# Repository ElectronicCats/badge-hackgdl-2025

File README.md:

# Badge HackGDL 2025

<p align="center">
    
</p>

<p align=center>
    
</p>

Welcome to the official repository of the Hack GDL 2025 event badge, developed by Electronic Cats. This portable device is designed to be interactive, educational, and hackable. It is based on the [Minino](https://github.com/ElectronicCats/Minino) platform, which uses ESP-IDF as the development environment and offers a modular system for creating BLE and Wi-Fi applications.

## Features:
- ESP32-S3
- Bluetooth Low Energy (BLE) + Wi-Fi
- USB-C for power and programming
- 4 x physical buttons for interaction
- 3 neopixel
- Integrated OLED Screen
- 3x AAA Battery Holder
- 1 x Buzzer
- Shitty Addon Connector
- Case
- Based on [Minino](https://github.com/ElectronicCats/Minino), with a modular architecture for multiple apps

## Included Applications:
These applications are ready-to-use and serve as a base for creating your own ideas during the event.
- Bluetooth (BLE) Applications
- Wi-Fi Applications
- Digital Tamagotchi

## Flashing Firmware:
Your badge should come with the latest firmware. If an update is required, this section of the wiki will explain how to flash your badge with the latest firmware. 

### Bootloader mode

To be able to flash your board, you will need to understand how to put it into bootloader mode. You just need to follow the sequence below:

* Press and hold the **BOOT** button
* Press and release the **RST** button
* Release the **BOOT** button

### ESP Tool (Web) update

1. Download the latest firmware from the [releases](https://github.com/ElectronicCats/badge-hackgdl-2025/releases) section.

2. Extract the downloaded file.

3. Open your web browser and go to [ESP Tool](https://espressif.github.io/esptool-js/).

4. Connect your badge to your computer using a USB cable and enter [bootloader mode](https://github.com/ElectronicCats/badge-hackgdl-2025/edit/main/README.md#bootloader-mode). 

5. Once on the page, in the baud rate, select 460800 and click on the “Connect” button.

6. You will see a pop-up window asking you to select the port where your badge is detected. Choose the one labeled “USB JTAG/serial debug unit.”

7. Once your badge is connected, the website will display the “Flash Address” field. Enter 0x0 in that field.

8. Click on “Select File” and look for the files in the unzipped folder. You must match the file and address according to the following table:

| Flash Address | File                 |
|---------------|----------------------|
| 0x0           | HackGDL_2025.bin |

9. Once you have all the files, click on “Program.” Wait until the process ends, or you read the message “Leaving...” in the output console.

10. When the program is finished, click on the “Disconnect” button.
11. Reset your HackGDL 2025 badge.

### Using the console

>[!IMPORTANT]
> [esptool.py](https://pypi.org/project/esptool/) is required.

To update your badge’s firmware, follow these steps:

1. Download the latest firmware from the [releases](https://github.com/ElectronicCats/badge-hackgdl-2025/releases).

3. Extract the downloaded file.

3. Open a terminal and navigate to the extracted folder. Make sure you see the HackGDL_2025.bin file.

4. Connect your badge to your computer using a USB cable and enter [bootloader mode](https://github.com/ElectronicCats/badge-hackgdl-2025/edit/main/README.md#bootloader-mode). Then check the port it is connected to.
    - **Windows**: Check it in the Device Manager under the Ports section.
    - **Linux**: check it with the `ls /dev/ttyUSB*` or `ls /dev/ttyACM*` command.
    - **macOS**: Check it with the `ls /dev/cu.usb*` command.

5. Run the following command to flash the firmware:

```python
python -m esptool --chip esp32s3 -b 460800 --before default_reset --after hard_reset write_flash --flash_mode dio --flash_size 4MB --flash_freq 80m 0x0 HackGDL_2025.bin
```

## Development Reference:

To compile, modify, or develop new applications for this badge, follow the official [Minino firmware development guide](https://github.com/ElectronicCats/Minino/tree/main/firmware).

> [!NOTE]  
> Although the Minino platform was designed for ESP32-C6, the HackGDL 2025 badge uses an ESP32-S3 as the main microcontroller. Make sure to configure the correct chip target in your development environment.

It includes:
ESP-IDF installation (v5.1.2)
Environment setup
Firmware compilation
Modular app structure
Flash and monitor commands

## FAQs
**Does the badge work out of the box?**

Yes. It comes with functional BLE and WiFi-based apps pre-installed.

**Can I develop my own app?**

Absolutely! Use Minino’s modular system and examples as a starting point.

**Where can I get help?**

Check the Minino wiki or open an issue [here](https://github.com/ElectronicCats/badge-hackgdl-2025/issues).

## Gratitude
Do you want to say thank you? Tag these companies on social networks and show them your badge, thanks to them, it is possible

- [ElectronicCats](https://electroniccats.com/)
- [HackGDL](https://hackgdl.net/)
- [Project TamaLib: A hardware-agnostic first-gen Tamagotchi emulation library](https://github.com/jcrona/tamalib)

## License

Electronic Cats invests time and resources providing this open source design, please support Electronic Cats and open-source hardware by purchasing products from Electronic Cats!

Designed by Electronic Cats.

Firmware released under an GNU AGPL v3.0 license. See the LICENSE file for more information.

Hardware released under an CERN Open Hardware License v1.2. See the LICENSE_HARDWARE file for more information.

Electronic Cats is a registered trademark, please do not use if you sell these PCBs.

Nov 29 2022

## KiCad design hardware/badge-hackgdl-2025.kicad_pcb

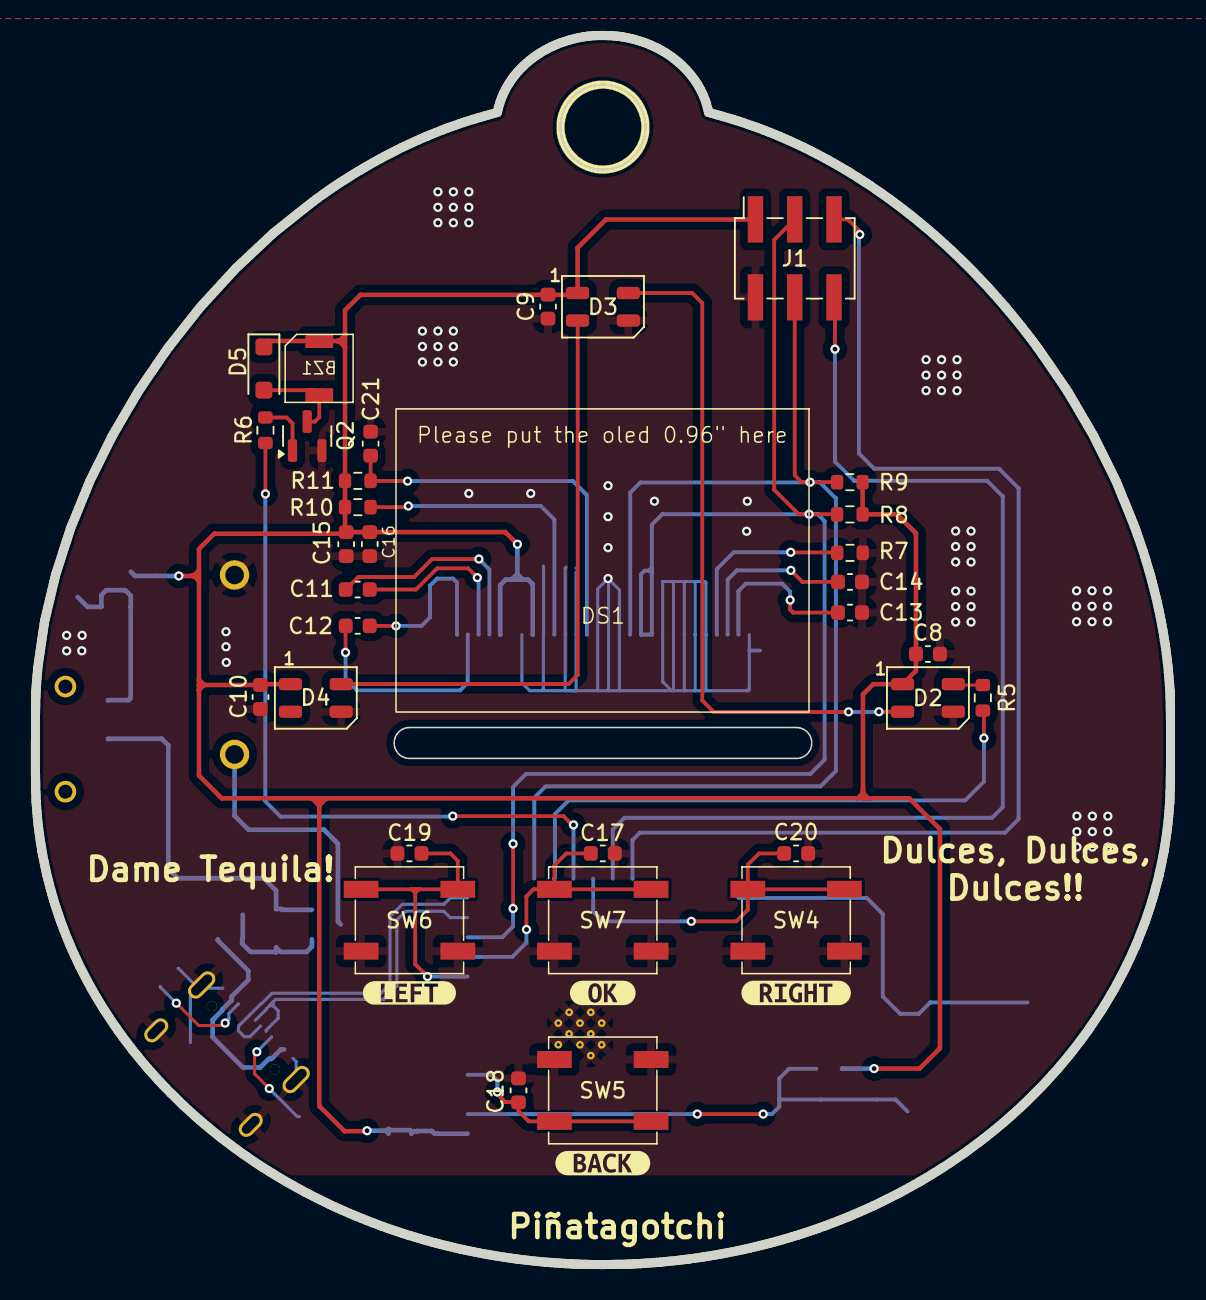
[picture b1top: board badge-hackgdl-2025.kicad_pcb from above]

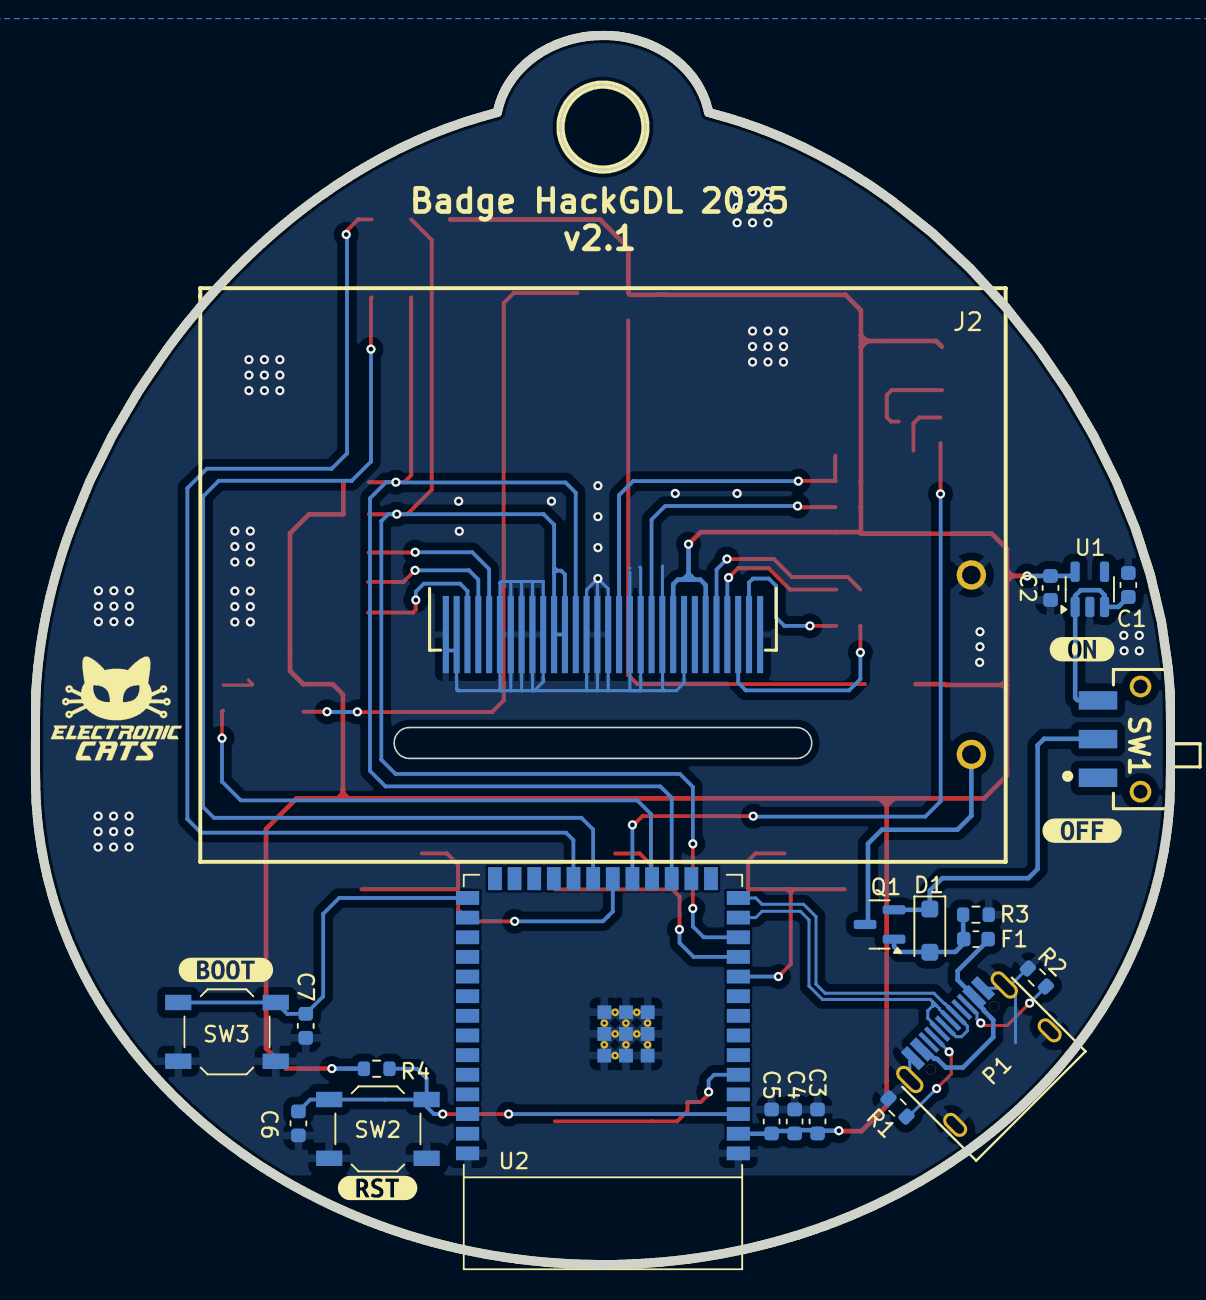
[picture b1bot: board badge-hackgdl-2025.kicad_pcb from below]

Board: 11 copper layers, 73.4 x 79.5 mm, 64 parts (26 on the bottom side), 37 nets.

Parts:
BZ1: Buzzer; Buzzer4x4
C1, C2, C4, C5, C13, C14, C16: 10uF; C_0603_1608Metric
C3, C11, C12: 1uF; C_0603_1608Metric
C6, C7, C8, C9, C10, C15, C17, C18, C19, C20: 100nF; C_0603_1608Metric
C21: 4.7uF; C_0603_1608Metric
D1, D5: MBR120; D_SOD-123F
D2, D3, D4: WS2812B; LED_WS2812B-Mini_PLCC4_3.5x3.5mm
DS1: OLED-128O064D; ssd1306_oled_conn_through_the_oled
F1: 1A; Fuse_0603_1608Metric
J1: ADDON; PinSocket_2x03_P2.54mm_Vertical_SMD
J2: Battery; BAT-TH_BH-AAA-A1AJ024
P1: USB_C_Plug_USB2.0; C393939
Q1: DMG3415U-7; SOT-23
Q2: MMBT2222A; SOT-23
R1, R2: 5k1; R_0603_1608Metric
R3: 100K; R_0603_1608Metric
R4, R8, R9, R10, R11: 10k; R_0603_1608Metric
R5: 470; R_0603_1608Metric
R6: 1K; R_0603_1608Metric
R7: 390k; R_0603_1608Metric
Ref**: Val**; badge-hackgdl-2025-Edge_Cuts
Ref**#2: Val**; badge-hackgdl-2025-Edge_Cuts
SW1: ON; JS102011SAQN
SW2: RESET; SW_SPST_TL3342
SW3: BOOT; SW_SPST_TL3342
SW4: RIGHT; Button_6.6x6.5
SW5: BACK; Button_6.6x6.5
SW6: LEFT; Button_6.6x6.5
SW7: MIDDLE; Button_6.6x6.5
U1: XC6220B331MR-G; SOT-23-5
U2: ESP32-S3-WROOM-1-N4; ESP32-S3-WROOM-1
kibuzzard-67883A3F: G***; kibuzzard-67883A3F
kibuzzard-67883A4C: G***; kibuzzard-67883A4C
kibuzzard-678830B0: G***; kibuzzard-678830B0
kibuzzard-678830B8: G***; kibuzzard-678830B8
kibuzzard-678830ED: G***; kibuzzard-678830ED
kibuzzard-678830F7: G***; kibuzzard-678830F7
kibuzzard-6789895F: G***; kibuzzard-6789895F
kibuzzard-67898922: G***; kibuzzard-67898922

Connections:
+3V3: BZ1.1 (-), C2.1, C3.1, C4.1, C5.1, C8.2, C9.2, C10.2, C15.1, C16.1, D2.1 (VDD), D3.1 (VDD), D4.1 (VDD), D5.1 (K), DS1.6 (VBAT), DS1.9 (VDD), J1.1, R4.2, R8.2, R9.2, R10.2, R11.2, U1.5 (VOUT), U2.2 (3V3)
+BATT: J2.2, Q1.3 (D)
/BACK: C18.1, SW5.2, U2.5 (IO5)
/BOOT: C7.1, SW3.2, U2.27 (IO0)
/Buzz: R6.1, U2.19 (IO11)
/D+: P1.A6 (D+), U2.14 (IO20)
/D-: P1.A7 (D-), U2.13 (IO19)
/GPIO1: J1.5, U2.22 (IO14)
/GPIO2: J1.6, U2.21 (IO13)
/LEFT: C19.1, SW6.2, U2.10 (IO17)
/MIDDLE: C17.1, SW7.2, U2.11 (IO18)
/NEOPIXEL: R5.1, U2.18 (IO10)
/RIGHT: C20.1, SW4.2, U2.20 (IO12)
/RST: C6.1, R4.1, SW2.2, U2.3 (EN)
/SCL: DS1.18 (D0), J1.4, R9.1, U2.17 (IO9)
/SDA: DS1.19 (D1), DS1.20 (D2), J1.3, R8.1, U2.12 (IO8)
GND: C1.2, C2.2, C3.2, C4.2, C5.2, C6.2, C7.2, C8.1, C9.1, C10.1, C13.1, C14.2, C15.2, C16.2, C17.2, C18.2, C19.2, C20.2, C21.2, D2.3 (VSS), D3.3 (VSS), D4.3 (VSS), DS1.1 (GND), DS1.8 (VSS), DS1.10 (BS0), DS1.12 (BS2), DS1.13 (~CS), DS1.15 (D/~C), DS1.16 (R/~W), DS1.17 (E/~RD), DS1.21 (D3), DS1.22 (D4), DS1.23 (D5), DS1.24 (D6), DS1.25 (D7), DS1.29 (VLSS), DS1.30 (GND), J1.2, J2.1, P1.A1 (GND), P1.S1 (SHIELD), Q2.2 (E), R1.1, R2.1, R3.2, R7.2, SW2.1, SW3.1, SW4.1, SW5.1, SW6.1, SW7.1, U1.2 (GND), U2.1 (GND), U2.40 (GND), U2.41 (GND)
unnamed: BZ1.2 (+), D5.2 (A), Q2.3 (C)
unnamed: D1.1 (K), Q1.2 (S), SW1.2 (B)
unnamed: D2.4 (DIN), R5.2
unnamed: D2.2 (DOUT), D3.4 (DIN)
unnamed: D3.2 (DOUT), D4.4 (DIN)
unnamed: DS1.11 (BS1), R10.1
unnamed: C11.1, DS1.5 (C1N)
unnamed: C11.2, DS1.4 (C1P)
unnamed: C12.2, DS1.2 (C2N)
unnamed: C12.1, DS1.3 (C2P)
unnamed: DS1.26 (IREF), R7.1
unnamed: C13.2, DS1.28 (VCC)
unnamed: C14.1, DS1.27 (VCOMH)
unnamed: C21.1, DS1.14 (~RES), R11.1
unnamed: F1.1, P1.A4 (VBUS)
unnamed: P1.A5 (CC), R1.2
unnamed: P1.B5 (VCONN), R2.2
unnamed: Q2.1 (B), R6.2
unnamed: C1.1, SW1.3 (A), U1.1 (VIN), U1.3 (EN)
VBUS: D1.2 (A), F1.2, Q1.1 (G), R3.1

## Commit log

2024-12-27 feat: add kicad project files
2024-12-27 feat: github actions modified
2024-12-27 feat(hw): add componnets for usb and microcontroller
2024-12-27 feat: Update gitignore
2024-12-27 refactor: delete backups
2024-12-27 feat(hw): add neopixels in the schematic
2024-12-27 feat(hw): add buttons and buzzer
2024-12-27 feat: add oled connector
2024-12-30 feat: add components in schematic
2025-01-03 feat: firmware setup
2025-01-03 feat: add components
2025-01-03 feat: add tamalib port for IDF
2025-01-03 feat: update dependencies & cmakelists
2025-01-03 feat: update tamalib_idf component cmakelists
2025-01-03 feat(hw): add floor plan
2025-01-03 feat: add tamagotchi app
2025-01-03 feat: add input queue
2025-01-06 feat: add menus navigation
2025-01-06 feat: add main icos
2025-01-06 feat(hw): add 3d models
2025-01-06 feat: add GPIOs shittyaddon connector
2025-01-07 refactor: simplify display code
2025-01-07 refactor: port tamagotchi display to mininos screen driver
2025-01-07 refactor: port menu navigation screen
2025-01-07 refactor: tamagotchi selection screen port
2025-01-08 feat(hw): update bom
2025-01-08 feat(hw): add 3d model for switch
2025-01-08 refactor: improve tamagotchi screen refresh to avoid alliasing
2025-01-08 feat: add generals & tamagotchi settings
2025-01-08 feat(hw): change oled footprint
2025-01-08 feat(hw): move buttons
2025-01-08 feat: improve menus UI
2025-01-08 refactor: general knob & general submenu to horizontal
2025-01-09 refactor: general radio selection UI to horizontal
2025-01-09 refactor: remove radio selection test code
2025-01-09 feat: add wifi apps
2025-01-09 feat: add BLE apps
2025-01-09 feat: launch BLE apps from menu
2025-01-09 refactor: menus & submenus UI
2025-01-10 feat: scrolling text to horizontal
2025-01-10 feat: add animations
2025-01-10 fix: tamagotchi display selection bitmaps
2025-01-10 refactor: summary scrolling text
2025-01-10 feat(hw): add routes in pcb
2025-01-13 refactor: notification function name
2025-01-13 refactor: HID app using generals
2025-01-13 feat: add general notification
2025-01-13 feat(hw): change ON/OFF switch
2025-01-13 refactor: HID menus
2025-01-13 fix: general notification bugs
2025-01-13 refactor: adv scanner using generals
2025-01-14 fix: general knob exit
2025-01-14 feat(hw): add labels
2025-01-14 feat(hw): change size of pads in the oled footprint
2025-01-14 feat(hw): change routes in oled
2025-01-14 refactor: trakers module
2025-01-14 refactor: deauth main menu
2025-01-14 refactor: deauth ap selection
2025-01-14 refactor: deauth attack selection
2025-01-14 feat: improve deauth main menu feeling
2025-01-14 refactor: deauth captive portal selection UI
2025-01-14 refactor: captive portal input
2025-01-14 refactor(hw): move buttons
2025-01-15 feat(hw): add space between buttons
2025-01-15 fix(hw): change gpio pins for addon connector
2025-01-15 fix(hw): change left button to gpio 17
2025-01-15 feat: improve main app scenes feeling
2025-01-15 fix: trakers count
2025-01-15 feat(hw): add capacitor in reset pin
2025-01-15 feat: trakers list bug test
2025-01-15 fix: deauth Rogue AP attack
2025-01-15 feat(hw): change LDO position
2025-01-15 feat(hw): change F1 position
2025-01-15 feat(hw): case parts
2025-01-15 feat: add wifi apps icons
2025-01-16 feat(hw): increase tolerances
2025-01-16 feat: add bluetooth apps icons
2025-01-16 feat: add rectangle on menu icons
2025-01-16 feat (hw): increase lid height
2025-01-16 feat: add neopixels
2025-01-16 refactor: change neopixels count
2025-01-16 refactor: tamagotchi UI
2025-01-17 feat: add set tama nickname cmd
2025-01-17 feat: save nickname in flash memory
2025-01-21 feat: add espnow connection
2025-01-21 feat: using espnow without dependencies
2025-01-22 feat: add tamagotchi friends logic
2025-01-22 feat: tamagotchi friends found logic
2025-01-22 feat: display friends count
2025-01-22 fix: avoid empty macs
2025-01-22 feat: show friends list
2025-01-22 fix: tama now & tama display deinit
2025-01-23 feat: add tamagotchi help menus
2025-01-23 feat: confirm tamagotchi erase
2025-01-23 feat(hw): update button
2025-01-23 feat(hw): change components in BOM
2025-01-23 chore: add pinata pitures
2025-01-23 chore: change hand location
2025-01-23 feat(hw): add 3d model for pcb
2025-01-23 feat: add animations module thread safe
2025-01-24 feat: improve animations module & add animation test
2025-01-24 feat: show splash screen
2025-01-24 feat: add fade out function
2025-01-24 feat: add loading bar
2025-01-24 feat: add animations module exit cb
2025-01-24 feat: add friends scanner menu
2025-01-25 feat: add scanning animations
2025-01-27 refactor(hw): change routes width
2025-01-27 feat: scanning logic completed
2025-01-27 refactor: update tamagotchi friends help
2025-01-27 feat(hw): new buttons case design
2025-01-27 refactor: update tamagotchi nickname help
2025-01-28 feat: add about menus
2025-01-28 feat: add about inf
2025-01-28 feat: update kconfig
2025-01-28 feat: update keyboard labels on kconfig
2025-01-28 refactor(hw): switch approached the edge of the pcb
2025-01-28 feat: add esp32c6 support
2025-01-28 fix: show friends nickname List
2025-01-28 refactor: remove new test menu
2025-01-29 feat: disable input while deauth scanning
2025-01-29 fix(hw): add GND path and change the oled footprint side
2025-01-29 fix: buzzer stack overflow & update credits
2025-01-29 fix: deauth scanning task on S3
2025-01-29 feat: show restart message on screen
2025-01-29 feat: Create LICENSE_HARDWARE.md
2025-01-29 docs: Update README.md
2025-01-30 feat: add noepixels ctrl bases & knob rect widget
2025-01-30 feat: neopixels ctrl logic
2025-01-30 feat: neopixels ctr GUI
2025-01-30 feat: neopixels app finished
2025-01-31 feat: add neopixels icon & master neopixel control
2025-01-31 feat: add web file manager
2025-01-31 feat: increase flash file system partition space
2025-02-20 fix: avoid playing buzzer with null freq
2025-02-25 refactor: Neopixels order
2025-02-25 refactor: set esp32S3 on make file
2025-05-06 feat: file manager module was added
2025-05-08 feat: file manager module dependencies was added
2025-05-08 fix: make compile OK
2025-05-08 test: local file manager was temporarily added to the main menu
2025-05-09 fix: file manager menu OK
2025-05-09 fix: back button ok in local file manager
2025-05-15 feat: add important information
2025-05-19 feat: add sections for more information on readme
2025-05-19 fix: format and links
2025-05-20 fix: typo README.md
